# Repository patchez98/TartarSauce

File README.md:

# TartarSauce
Replacement for Razer Nostromo / Tartarus / Orbweaver with mechanical switches and analog thumbstick

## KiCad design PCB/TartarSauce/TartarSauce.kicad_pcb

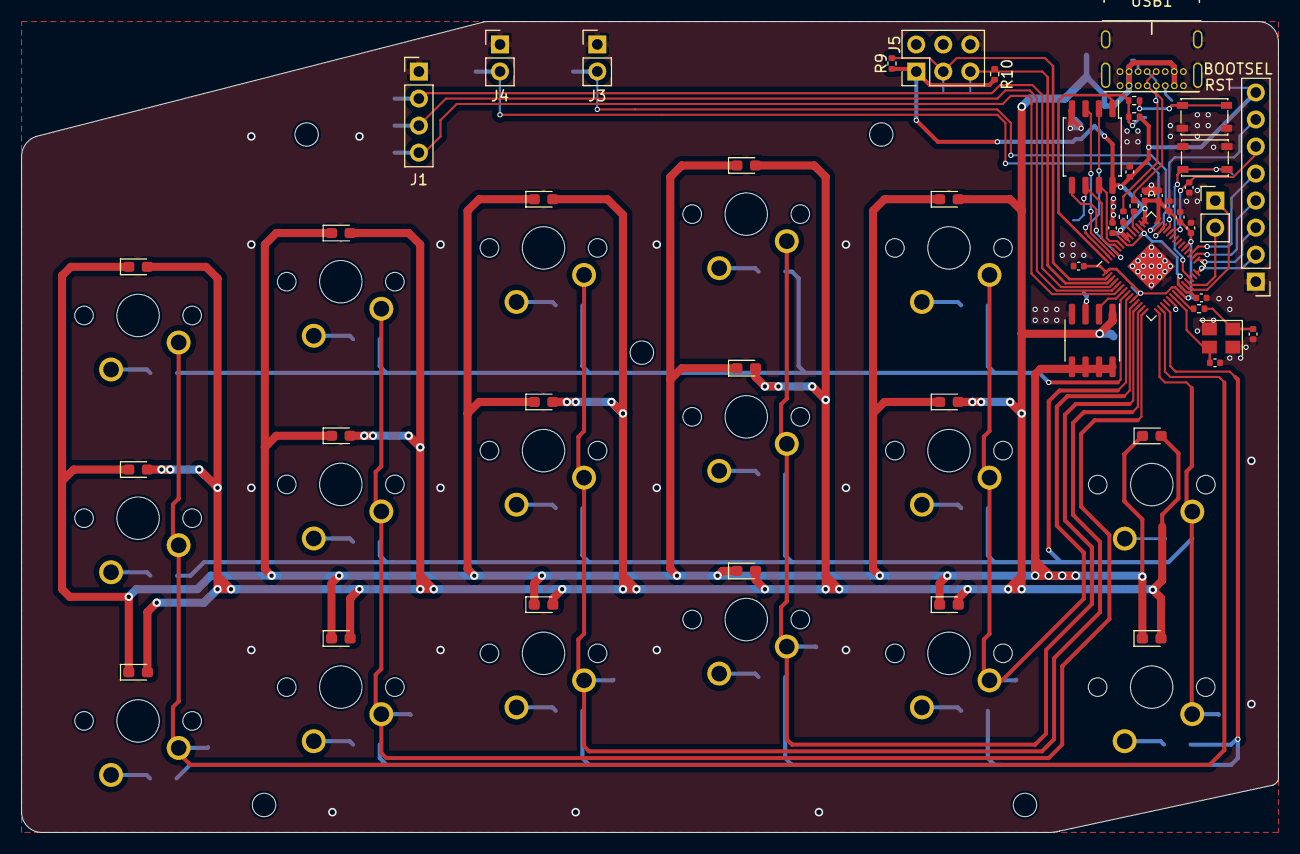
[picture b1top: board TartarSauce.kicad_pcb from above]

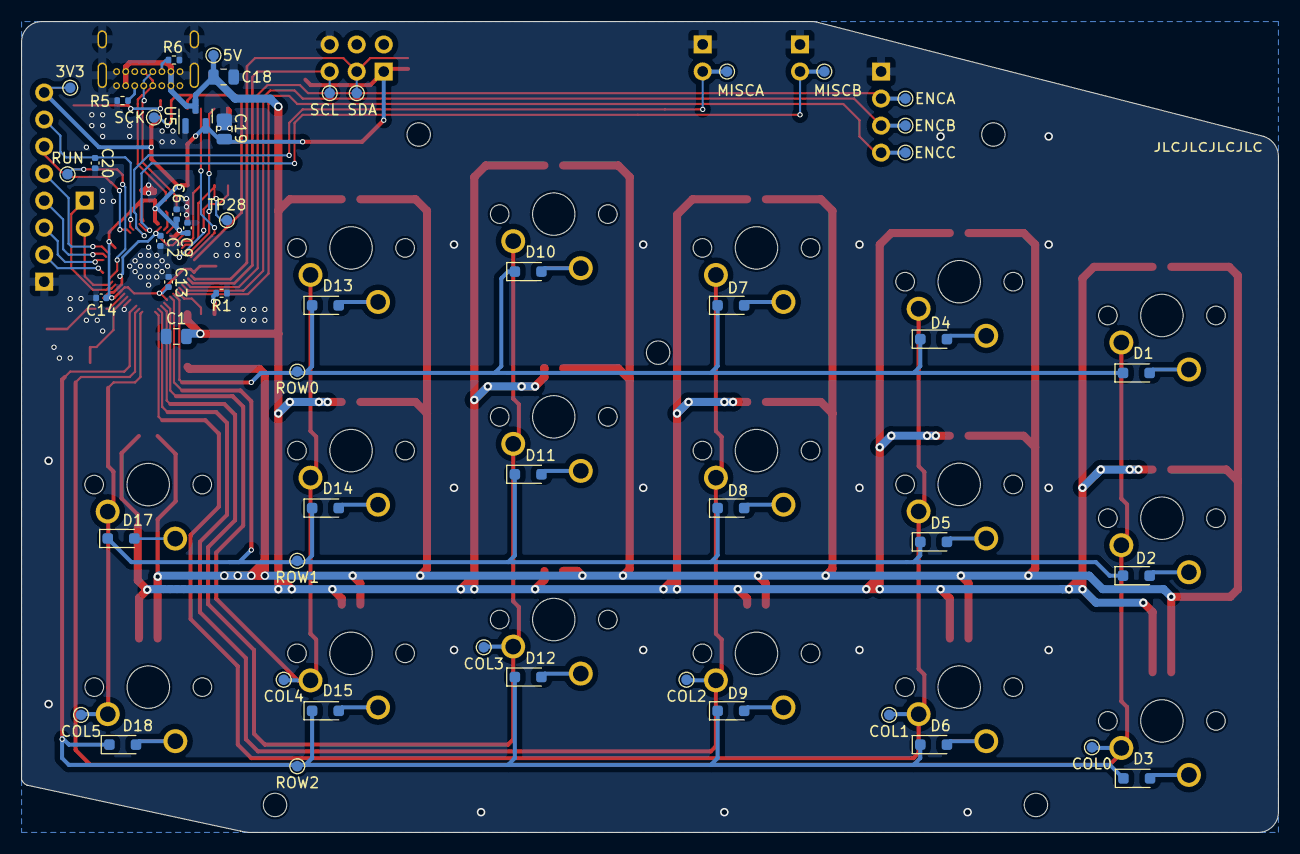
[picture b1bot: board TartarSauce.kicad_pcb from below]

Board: 2 copper layers, 118.1 x 76.2 mm, 100 parts (51 on the bottom side), 65 nets.

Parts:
C1, C18, C19: 10u; C_0805_2012Metric
C2, C5: 1u; C_0402_1005Metric
C3, C4, C6, C7, C8, C9, C10, C11, C12, C13, C14, C15: 0.1u; C_0402_1005Metric
C16, C17: 27p; C_0402_1005Metric
C20, C21: 1n; C_0402_1005Metric
D1, D2, D3, D4, D5, D6, D7, D8, D9, D10, D11, D12, D13, D14, D15, D17, D18: D; D_SOD-323_HandSoldering
J1: Encoder; PinHeader_1x04_P2.54mm_Vertical
J2: Thumbstick; PinHeader_1x08_P2.54mm_Vertical
J3, J4: MISC_A; PinHeader_1x02_P2.54mm_Vertical
J5: OLED; PinHeader_2x03_P2.54mm_Vertical
J6: DBG; PinHeader_1x02_P2.54mm_Vertical
MX1, MX2, MX3, MX4, MX5, MX6, MX7, MX8, MX9, MX10, MX11, MX12, MX13, MX14, MX15, MX17, MX18: MX-LED; MXOnly-1U
R1: 16k; R_0402_1005Metric
R2: DNP; R_0402_1005Metric
R3, R4: 1k; R_0402_1005Metric
R5, R6, R9, R10: 5k1; R_0402_1005Metric
R7, R8: 27R; R_0402_1005Metric
SW1: BOOTSEL; SW_SPST_PTS810
SW2: RST; SW_SPST_PTS810
TP1: ROW0; TestPoint_Pad_D1.0mm
TP2: ROW1; TestPoint_Pad_D1.0mm
TP3: ROW2; TestPoint_Pad_D1.0mm
TP4: COL0; TestPoint_Pad_D1.0mm
TP5: COL1; TestPoint_Pad_D1.0mm
TP6: COL2; TestPoint_Pad_D1.0mm
TP7: COL3; TestPoint_Pad_D1.0mm
TP8: COL4; TestPoint_Pad_D1.0mm
TP9: COL5; TestPoint_Pad_D1.0mm
TP10: SDA; TestPoint_Pad_D1.0mm
TP11: SCL; TestPoint_Pad_D1.0mm
TP13: ENCA; TestPoint_Pad_D1.0mm
TP14: ENCB; TestPoint_Pad_D1.0mm
TP15: ENCC; TestPoint_Pad_D1.0mm
TP16: MISCA; TestPoint_Pad_D1.0mm
TP17: MISCB; TestPoint_Pad_D1.0mm
TP28, TP29: SCK; TestPoint_Pad_D1.0mm
TP31: RUN; TestPoint_Pad_D1.0mm
TP32: 5V; TestPoint_Pad_D1.0mm
TP33: 3V3; TestPoint_Pad_D1.0mm
U2: MIC4801; SOIC-8_3.9x4.9mm_P1.27mm
U3: RP2040; QFN-56-1EP_7x7mm_P0.4mm_EP3.2x3.2mm
U4: W25Q128JVS; SOIC-8_5.23x5.23mm_P1.27mm
U5: AP2127N-3.3; SOT-23
USB1: USB4085-GF-A-Type-C; USB_C_GCT_USB4085
Y1: 12MHz_18pf_30ppm; Crystal_SMD_3225-4Pin_3.2x2.5mm

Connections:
+1V1: C2.1, C3.1, C4.1, U3.23 (DVDD), U3.45 (VREG_VOUT), U3.50 (DVDD)
+3V3: C5.1, C6.1, C7.1, C8.1, C9.1, C10.1, C11.1, C12.1, C13.1, C14.1, C15.1, C19.1, J2.8, J5.1, R2.2, R9.2, R10.2, TP33.1, U3.1 (IOVDD), U3.10 (IOVDD), U3.22 (IOVDD), U3.33 (IOVDD), U3.42 (IOVDD), U3.43 (ADC_AVDD), U3.44 (VREG_IN), U3.48 (USB_VDD), U3.49 (IOVDD), U4.8 (VCC), U5.2 (VO)
+5V: C1.2, C18.1, MX1.3 (LED), MX2.3 (LED), MX3.3 (LED), MX4.3 (LED), MX5.3 (LED), MX6.3 (LED), MX7.3 (LED), MX8.3 (LED), MX9.3 (LED), MX10.3 (LED), MX11.3 (LED), MX12.3 (LED), MX13.3 (LED), MX14.3 (LED), MX15.3 (LED), MX17.3 (LED), MX18.3 (LED), TP32.1, U2.1 (VIN), U5.3 (VI), USB1.A4 (VBUS), USB1.A9 (VBUS), USB1.B4 (VBUS), USB1.B9 (VBUS)
/Col0: MX1.1 (COL), MX2.1 (COL), MX3.1 (COL), TP4.1, U3.16 (GPIO13)
/Col1: MX4.1 (COL), MX5.1 (COL), MX6.1 (COL), TP5.1, U3.14 (GPIO11)
/Col2: MX7.1 (COL), MX8.1 (COL), MX9.1 (COL), TP6.1, U3.13 (GPIO10)
/Col3: MX10.1 (COL), MX11.1 (COL), MX12.1 (COL), TP7.1, U3.12 (GPIO9)
/Col4: MX13.1 (COL), MX14.1 (COL), MX15.1 (COL), TP8.1, U3.11 (GPIO8)
/Col5: MX17.1 (COL), MX18.1 (COL), TP9.1, U3.15 (GPIO12)
/ENCODER_A: J1.2, TP13.1, U3.4 (GPIO2)
/ENCODER_B: J1.3, TP14.1, U3.5 (GPIO3)
/ENCODER_C: J1.4, TP15.1, U3.6 (GPIO4)
/LED_CAT: MX1.4 (LEDGND), MX2.4 (LEDGND), MX3.4 (LEDGND), MX4.4 (LEDGND), MX5.4 (LEDGND), MX6.4 (LEDGND), MX7.4 (LEDGND), MX8.4 (LEDGND), MX9.4 (LEDGND), MX10.4 (LEDGND), MX11.4 (LEDGND), MX12.4 (LEDGND), MX13.4 (LEDGND), MX14.4 (LEDGND), MX15.4 (LEDGND), MX17.4 (LEDGND), MX18.4 (LEDGND), U2.5 (Din), U2.6 (Din), U2.7 (Din), U2.8 (Din)
/LED_EN: U2.2 (EN), U3.7 (GPIO5)
/MISC_A: J3.2, TP16.1, U3.40 (GPIO28_ADC2)
/MISC_B: J4.2, TP17.1, U3.41 (GPIO29_ADC3)
/OLED_I2C_SCL: J5.5, R10.1, TP11.1, U3.3 (GPIO1)
/OLED_I2C_SDA: J5.3, R9.1, TP10.1, U3.2 (GPIO0)
/QSPI_CS: R2.1, R3.1, TP29.1, U3.56 (QSPI_SS), U4.1 (~CS)
/QSPI_SCLK: TP28.1, U3.52 (QSPI_SCLK), U4.6 (CLK)
/QSPI_SD0: U3.53 (QSPI_SD0), U4.5 (DI(IO0))
/QSPI_SD1: U3.55 (QSPI_SD1), U4.2 (DO(IO1))
/QSPI_SD2: U3.54 (QSPI_SD2), U4.3 (IO2)
/QSPI_SD3: U3.51 (QSPI_SD3), U4.7 (IO3)
/Row0: D1.1 (K), D4.1 (K), D7.1 (K), D10.1 (K), D13.1 (K), TP1.1, U3.8 (GPIO6)
/Row1: D2.1 (K), D5.1 (K), D8.1 (K), D11.1 (K), D14.1 (K), D17.1 (K), TP2.1, U3.9 (GPIO7)
/Row2: D3.1 (K), D6.1 (K), D9.1 (K), D12.1 (K), D15.1 (K), D18.1 (K), TP3.1, U3.17 (GPIO14)
/THUMB_AX_DX+: C21.1, J2.6, U3.38 (GPIO26_ADC0)
/THUMB_AY_DY+: C20.1, J2.7, U3.39 (GPIO27_ADC1)
/THUMB_DX-: J2.4, U3.30 (GPIO19)
/THUMB_DY-: J2.5, U3.31 (GPIO20)
/THUMB_JMP: J2.2, U3.28 (GPIO17)
/THUMB_L3: J2.3, U3.29 (GPIO18)
/USB_D+: R8.1, USB1.A6 (D+), USB1.B6 (D+)
/USB_D-: R7.1, USB1.A7 (D-), USB1.B7 (D-)
/~USB_BOOT: R3.2, SW1.1
GND: C1.1, C2.2, C3.2, C4.2, C5.2, C6.2, C7.2, C8.2, C9.2, C10.2, C11.2, C12.2, C13.2, C14.2, C15.2, C16.1, C17.1, C18.2, C19.2, C20.2, C21.2, J1.1, J2.1, J3.1, J4.1, J5.6, R1.1, R5.1, R6.1, SW1.2, SW2.2, U2.4 (GND), U3.19 (TESTEN), U3.57 (GND), U4.4 (GND), U5.1 (GND), USB1.A1 (GND), USB1.A12 (GND), USB1.B1 (GND), USB1.B12 (GND), USB1.S1 (Shell1), Y1.2, Y1.4
unnamed: C17.2, R4.2, Y1.1
unnamed: D1.2 (A), MX1.2 (ROW)
unnamed: D2.2 (A), MX2.2 (ROW)
unnamed: D3.2 (A), MX3.2 (ROW)
unnamed: D4.2 (A), MX4.2 (ROW)
unnamed: D5.2 (A), MX5.2 (ROW)
unnamed: D6.2 (A), MX6.2 (ROW)
unnamed: D7.2 (A), MX7.2 (ROW)
unnamed: D8.2 (A), MX8.2 (ROW)
unnamed: D9.2 (A), MX9.2 (ROW)
unnamed: D10.2 (A), MX10.2 (ROW)
unnamed: D11.2 (A), MX11.2 (ROW)
unnamed: D12.2 (A), MX12.2 (ROW)
unnamed: D13.2 (A), MX13.2 (ROW)
unnamed: D14.2 (A), MX14.2 (ROW)
unnamed: D15.2 (A), MX15.2 (ROW)
unnamed: D17.2 (A), MX17.2 (ROW)
unnamed: D18.2 (A), MX18.2 (ROW)
unnamed: J6.1, U3.24 (SWCLK)
unnamed: J6.2, U3.25 (SWD)
unnamed: R1.2, U2.3 (RSET)
unnamed: SW2.1, TP31.1, U3.26 (RUN)
unnamed: R7.2, U3.46 (USB_DM)
unnamed: R8.2, U3.47 (USB_DP)
unnamed: C16.2, U3.20 (XIN), Y1.3
unnamed: R4.1, U3.21 (XOUT)
unnamed: R5.2, USB1.A5 (CC1)
unnamed: R6.2, USB1.B5 (CC2)

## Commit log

2021-07-18 V2 completed, now includes diodes on all switches like it should have in the first place. Layout changed to be more ergonomic.
2021-07-18 Minor zone fill changes
2021-11-21 Changed project to PlatformIO, added bitmaps and saved STL files to repo
2021-12-30 Keymapping and analog stick functional
2021-12-30 Added some PCB drawings for modeling purposes
2022-09-10 quick commit because I'm nuking my computer
2024-06-28 Joystick works now, but isn't scaled properly
